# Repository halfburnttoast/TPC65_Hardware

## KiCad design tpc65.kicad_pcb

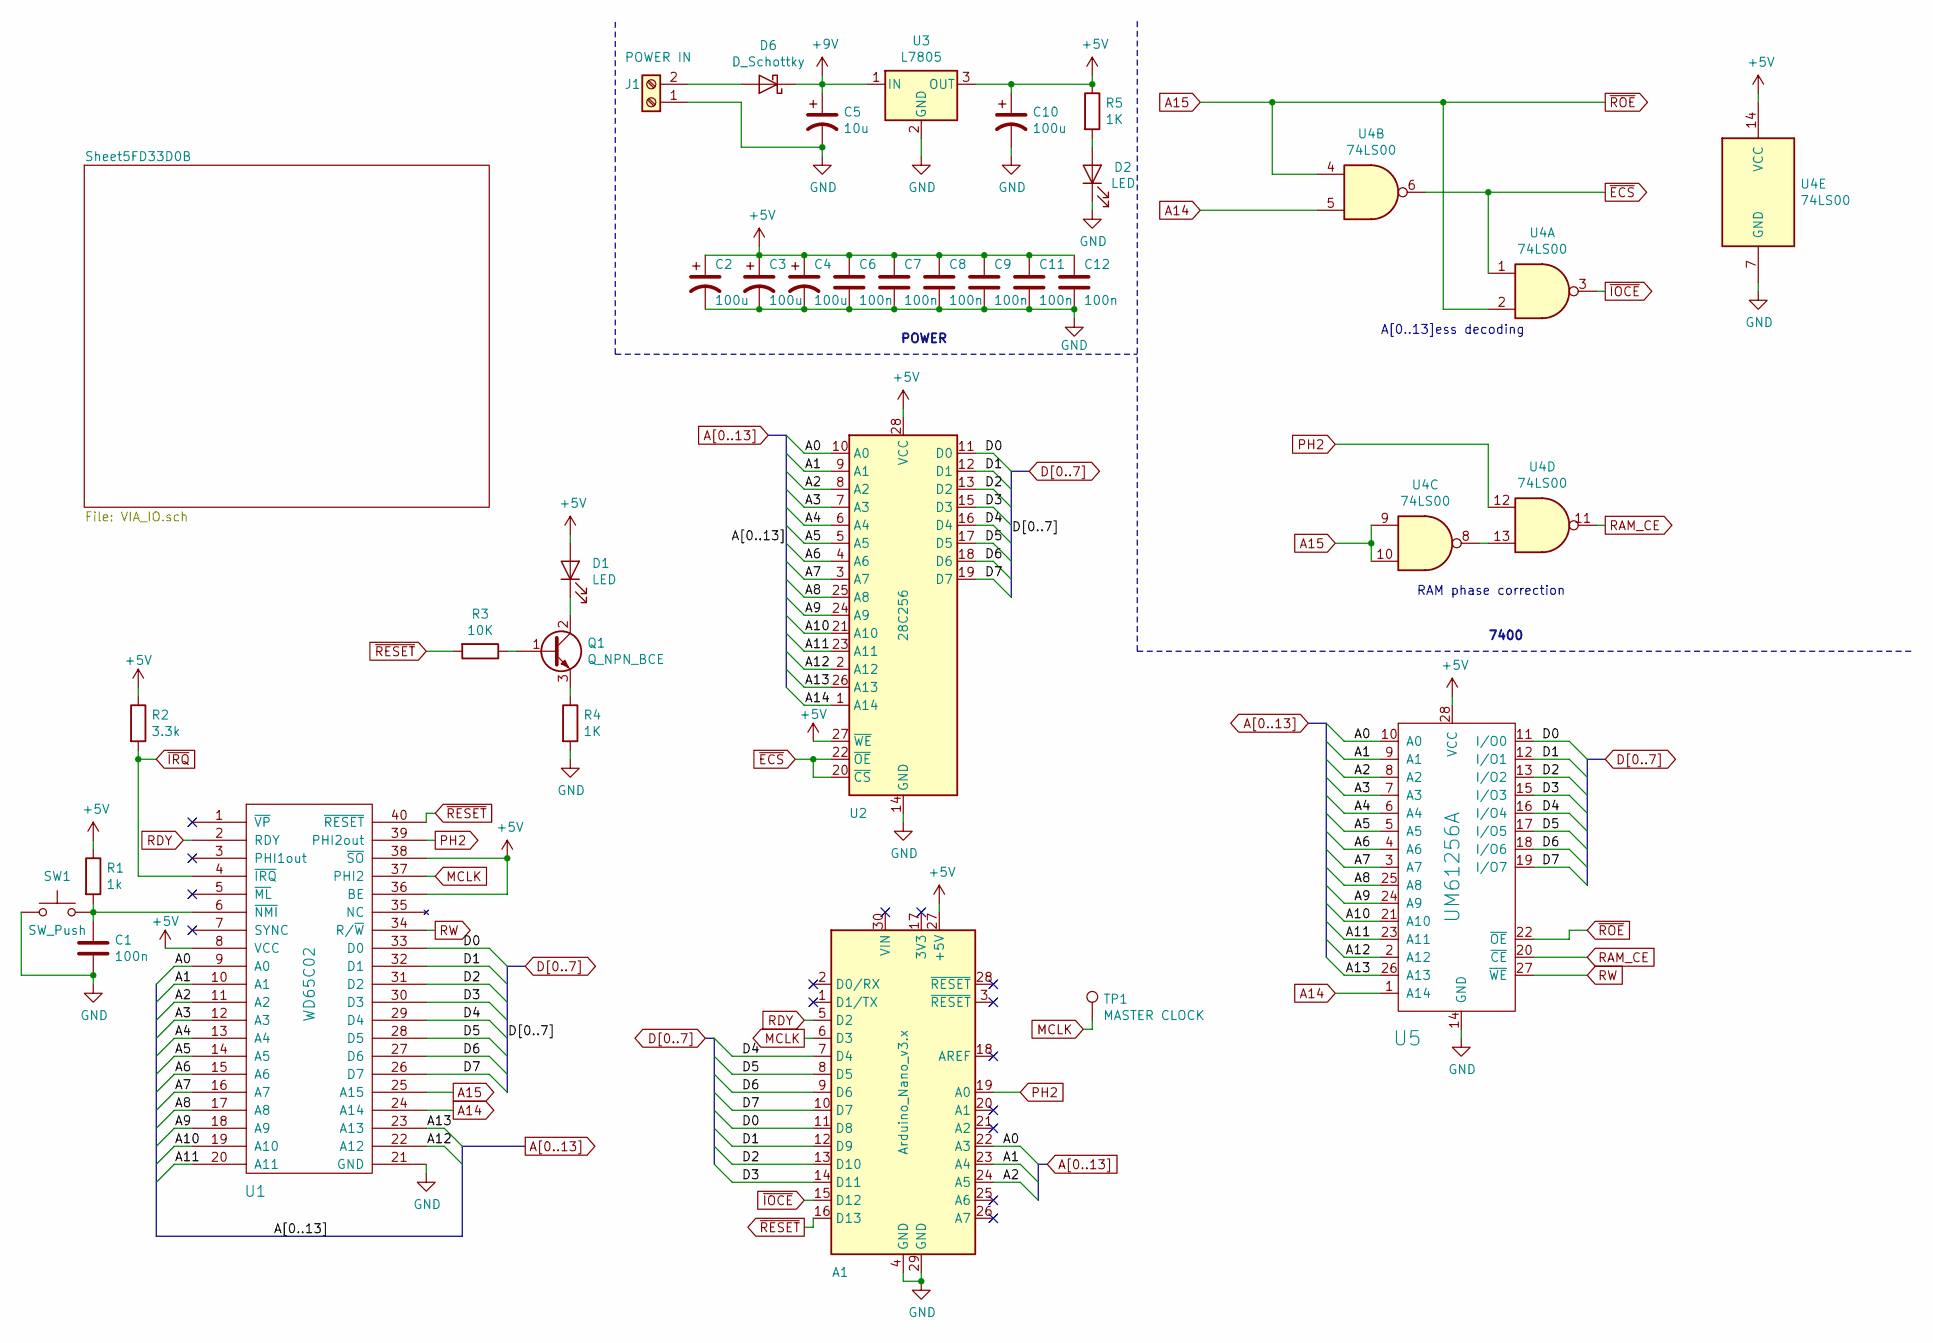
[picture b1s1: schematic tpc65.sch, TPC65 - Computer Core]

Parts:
A1: Arduino_Nano_v3.x; Arduino_Nano
C1, C6, C7, C8, C9, C11, C12: 100n; C_Disc_D4.3mm_W1.9mm_P5.00mm
C2, C3, C4, C10: 100u; CP_Radial_D5.0mm_P2.00mm
C5: 10u; CP_Radial_D5.0mm_P2.00mm
D1: LED; LED_1206_3216Metric_Pad1.42x1.75mm_HandSolder
D2: LED; LED_D5.0mm
D6: D_Schottky; D_SOD-123
J1: POWER IN; TerminalBlock_bornier-2_P5.08mm
Q1: Q_NPN_BCE; SOT-23_Handsoldering
R1: 1k; R_Axial_DIN0207_L6.3mm_D2.5mm_P7.62mm_Horizontal
R2: 3.3k; R_Axial_DIN0207_L6.3mm_D2.5mm_P7.62mm_Horizontal
R3: 10K; R_1206_3216Metric_Pad1.42x1.75mm_HandSolder
R4: 1K; R_1206_3216Metric_Pad1.42x1.75mm_HandSolder
R5: 1K; R_Axial_DIN0207_L6.3mm_D2.5mm_P7.62mm_Horizontal
SW1: SW_Push; SW_PUSH_6mm
TP1: MASTER CLOCK; TestPoint_Pad_1.0x1.0mm
U1: WD65C02; DIP-40_W15.24mm_Socket
U2: 28C256; DIP-28_W15.24mm_Socket
U3: L7805; TO-220F-3_Horizontal_TabDown
U4: 74LS00; DIP-14_W7.62mm_Socket
U5: UM61256A; DIP-28_W7.62mm_Socket

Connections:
+5V: A1.27 (+5V), C2.1, C3.1, C4.1, C6.1, C7.1, C8.1, C9.1, C10.1, C11.1, C12.1, D1.2 (A), R1.1, R2.1, R5.1, U1.8 (VCC), U1.36 (BE), U1.38 (~SO), U2.27 (~WE), U2.28 (VCC), U3.3 (OUT), U4.14 (VCC), U5.28 (VCC); also elsewhere on the board
+9V: C5.1, D6.1 (K), U3.1 (IN)
A0: A1.22 (A3), U1.9 (A0), U2.10 (A0), U5.10 (A0)
A1: A1.23 (A4), U1.10 (A1), U2.9 (A1), U5.9 (A1)
A2: A1.24 (A5), U1.11 (A2), U2.8 (A2), U5.8 (A2)
A3: U1.12 (A3), U2.7 (A3), U5.7 (A3); also elsewhere on the board
A4: U1.13 (A4), U2.6 (A4), U5.6 (A4); also elsewhere on the board
A5: U1.14 (A5), U2.5 (A5), U5.5 (A5); also elsewhere on the board
A6: U1.15 (A6), U2.4 (A6), U5.4 (A6); also elsewhere on the board
A7: U1.16 (A7), U2.3 (A7), U5.3 (A7); also elsewhere on the board
A8: U1.17 (A8), U2.25 (A8), U5.25 (A8); also elsewhere on the board
A9: U1.18 (A9), U2.24 (A9), U5.24 (A9)
A10: U1.19 (A10), U2.21 (A10), U5.21 (A10)
A11: U1.20 (A11), U2.23 (A11), U5.23 (A11)
A12: U1.22 (A12), U2.2 (A12), U5.2 (A12)
A13: U1.23 (A13), U2.26 (A13), U5.26 (A13)
A14: U1.24 (A14), U2.1 (A14), U4.5, U5.1 (A14)
A15: U1.25 (A15), U4.2, U4.4, U4.9, U4.10, U5.22 (~OE)
D0: A1.11 (D8), U1.33 (D0), U2.11 (D0), U5.11 (I/O0); also elsewhere on the board
D1: A1.12 (D9), U1.32 (D1), U2.12 (D1), U5.12 (I/O1); also elsewhere on the board
D2: A1.13 (D10), U1.31 (D2), U2.13 (D2), U5.13 (I/O2); also elsewhere on the board
D3: A1.14 (D11), U1.30 (D3), U2.15 (D3), U5.15 (I/O3); also elsewhere on the board
D4: A1.7 (D4), U1.29 (D4), U2.16 (D4), U5.16 (I/O4); also elsewhere on the board
D5: A1.8 (D5), U1.28 (D5), U2.17 (D5), U5.17 (I/O5); also elsewhere on the board
D6: A1.9 (D6), U1.27 (D6), U2.18 (D6), U5.18 (I/O6); also elsewhere on the board
D7: A1.10 (D7), U1.26 (D7), U2.19 (D7), U5.19 (I/O7); also elsewhere on the board
GND: A1.4 (GND), A1.29 (GND), C1.2, C2.2, C3.2, C4.2, C5.2, C6.2, C7.2, C8.2, C9.2, C10.2, C11.2, C12.2, D2.1 (K), J1.1, R4.2, SW1.1, U1.21 (GND), U2.14 (GND), U3.2 (GND), U4.7 (GND), U5.14 (GND); also elsewhere on the board
MCLK: A1.6 (D3), TP1.1, U1.37 (PHI2)
unnamed: C1.1, R1.2, SW1.2, U1.6 (~NMI)
unnamed: D1.1 (K), Q1.2 (C)
unnamed: D2.2 (A), R5.2
unnamed: D6.2 (A), J1.2
unnamed: Q1.1 (B), R3.1
unnamed: Q1.3 (E), R4.1
unnamed: U4.8, U4.13
PH2: A1.19 (A0), U1.39 (PHI2out), U4.12; also elsewhere on the board
RAM_CE: U4.11, U5.20 (~CE)
RDY: A1.5 (D2), U1.2 (RDY)
RW: U1.34 (R/~W), U5.27 (~WE); also elsewhere on the board
~ECS: U2.20 (~CS), U2.22 (~OE), U4.1, U4.6
~IOCE: A1.15 (D12), U4.3; also elsewhere on the board
~IRQ: R2.2, U1.4 (~IRQ); also elsewhere on the board
~RESET: A1.16 (D13), R3.2, U1.40 (~RESET); also elsewhere on the board

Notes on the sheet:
RAM phase correction
A[0..13]ess decoding
7400
POWER

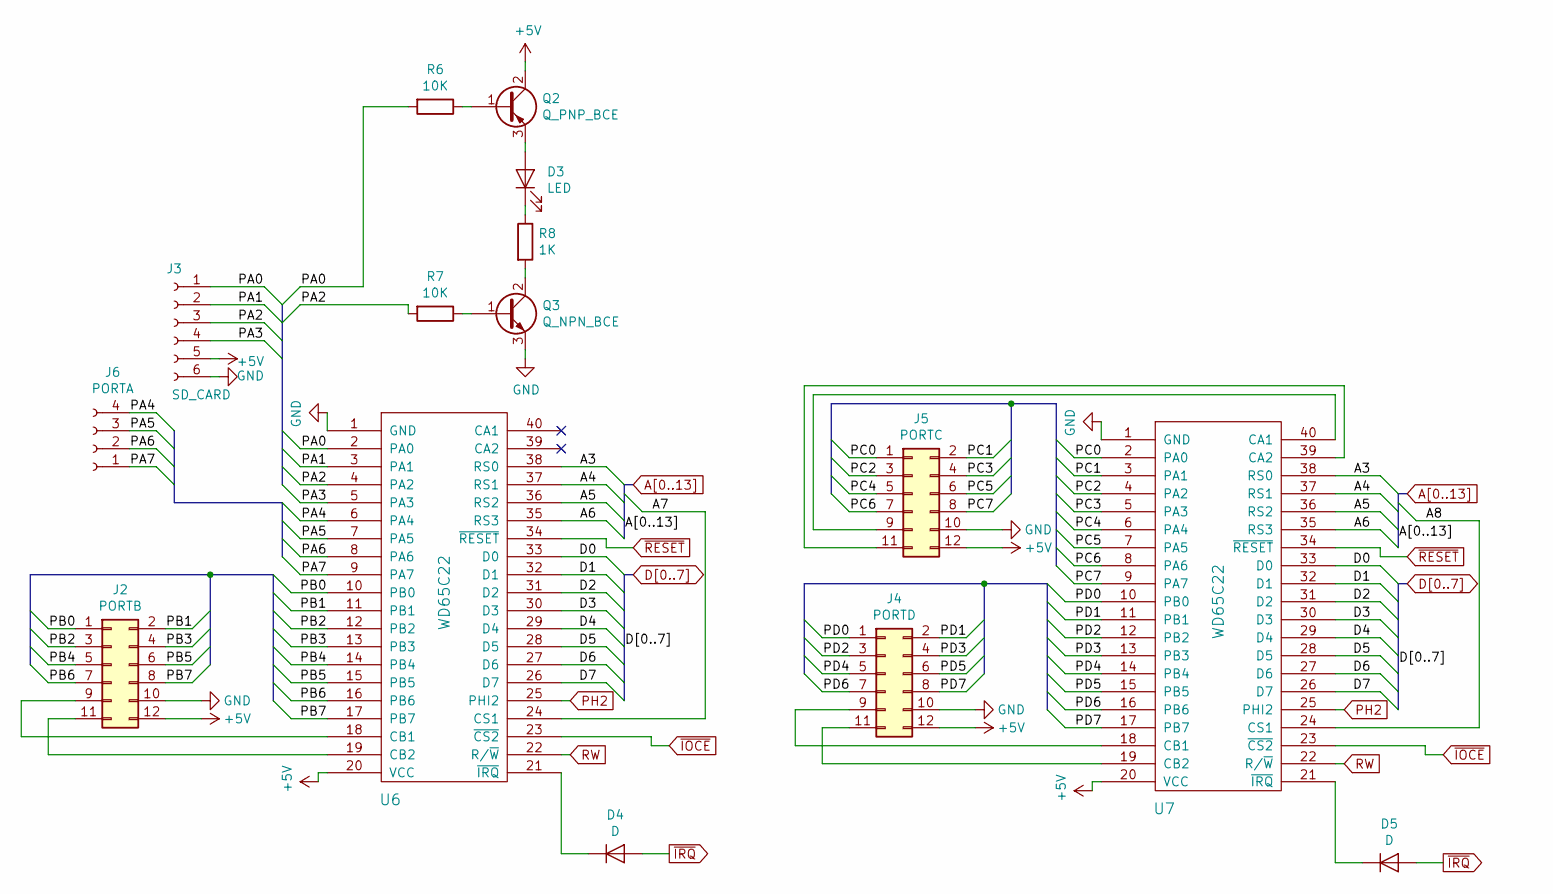
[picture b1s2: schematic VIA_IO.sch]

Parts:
D3: LED; LED_1206_3216Metric_Pad1.42x1.75mm_HandSolder
D4, D5: D; D_T-1_P5.08mm_Horizontal
J2: PORTB; PinSocket_2x06_P2.54mm_Vertical
J3: SD_CARD; PinSocket_1x06_P2.54mm_Vertical
J4: PORTD; PinSocket_2x06_P2.54mm_Vertical
J5: PORTC; PinSocket_2x06_P2.54mm_Vertical
J6: PORTA; PinSocket_2x02_P2.54mm_Vertical
Q2: Q_PNP_BCE; SOT-23_Handsoldering
Q3: Q_NPN_BCE; SOT-23_Handsoldering
R6, R7: 10K; R_1206_3216Metric_Pad1.42x1.75mm_HandSolder
R8: 1K; R_1206_3216Metric_Pad1.42x1.75mm_HandSolder
U6, U7: WD65C22; DIP-40_W15.24mm_Socket

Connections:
+5V: J2.12, J3.5, J4.12, J5.12, Q2.2 (C), U6.20 (VCC), U7.20 (VCC); also elsewhere on the board
/Sheet5FD33D0B/PA0: J3.1, R6.2, U6.2 (PA0)
/Sheet5FD33D0B/PA1: J3.2, U6.3 (PA1)
/Sheet5FD33D0B/PA2: J3.3, R7.2, U6.4 (PA2)
/Sheet5FD33D0B/PA3: J3.4, U6.5 (PA3)
/Sheet5FD33D0B/PA4: J6.4, U6.6 (PA4)
/Sheet5FD33D0B/PA5: J6.3, U6.7 (PA5)
/Sheet5FD33D0B/PA6: J6.2, U6.8 (PA6)
/Sheet5FD33D0B/PA7: J6.1, U6.9 (PA7)
/Sheet5FD33D0B/PB0: J2.1, U6.10 (PB0)
/Sheet5FD33D0B/PB1: J2.2, U6.11 (PB1)
/Sheet5FD33D0B/PB2: J2.3, U6.12 (PB2)
/Sheet5FD33D0B/PB3: J2.4, U6.13 (PB3)
/Sheet5FD33D0B/PB4: J2.5, U6.14 (PB4)
/Sheet5FD33D0B/PB5: J2.6, U6.15 (PB5)
/Sheet5FD33D0B/PB6: J2.7, U6.16 (PB6)
/Sheet5FD33D0B/PB7: J2.8, U6.17 (PB7)
/Sheet5FD33D0B/PC0: J5.1, U7.2 (PA0)
/Sheet5FD33D0B/PC1: J5.2, U7.3 (PA1)
/Sheet5FD33D0B/PC2: J5.3, U7.4 (PA2)
/Sheet5FD33D0B/PC3: J5.4, U7.5 (PA3)
/Sheet5FD33D0B/PC4: J5.5, U7.6 (PA4)
/Sheet5FD33D0B/PC5: J5.6, U7.7 (PA5)
/Sheet5FD33D0B/PC6: J5.7, U7.8 (PA6)
/Sheet5FD33D0B/PC7: J5.8, U7.9 (PA7)
/Sheet5FD33D0B/PD0: J4.1, U7.10 (PB0)
/Sheet5FD33D0B/PD1: J4.2, U7.11 (PB1)
/Sheet5FD33D0B/PD2: J4.3, U7.12 (PB2)
/Sheet5FD33D0B/PD3: J4.4, U7.13 (PB3)
/Sheet5FD33D0B/PD4: J4.5, U7.14 (PB4)
/Sheet5FD33D0B/PD5: J4.6, U7.15 (PB5)
/Sheet5FD33D0B/PD6: J4.7, U7.16 (PB6)
/Sheet5FD33D0B/PD7: J4.8, U7.17 (PB7)
A3: U6.38 (RS0), U7.38 (RS0); also elsewhere on the board
A4: U6.37 (RS1), U7.37 (RS1); also elsewhere on the board
A5: U6.36 (RS2), U7.36 (RS2); also elsewhere on the board
A6: U6.35 (RS3), U7.35 (RS3); also elsewhere on the board
A7: U6.24 (CS1); also elsewhere on the board
A8: U7.24 (CS1); also elsewhere on the board
D0: U6.33 (D0), U7.33 (D0); also elsewhere on the board
D1: U6.32 (D1), U7.32 (D1); also elsewhere on the board
D2: U6.31 (D2), U7.31 (D2); also elsewhere on the board
D3: U6.30 (D3), U7.30 (D3); also elsewhere on the board
D4: U6.29 (D4), U7.29 (D4); also elsewhere on the board
D5: U6.28 (D5), U7.28 (D5); also elsewhere on the board
D6: U6.27 (D6), U7.27 (D6); also elsewhere on the board
D7: U6.26 (D7), U7.26 (D7); also elsewhere on the board
GND: J2.10, J3.6, J4.10, J5.10, Q3.3 (E), U6.1 (GND), U7.1 (GND); also elsewhere on the board
unnamed: D3.1 (K), R8.1
unnamed: D3.2 (A), Q2.3 (E)
unnamed: D4.1 (K), U6.21 (~IRQ)
unnamed: D5.1 (K), U7.21 (~IRQ)
unnamed: J2.9, U6.18 (CB1)
unnamed: J2.11, U6.19 (CB2)
unnamed: J4.9, U7.18 (CB1)
unnamed: J4.11, U7.19 (CB2)
unnamed: J5.9, U7.40 (CA1)
unnamed: J5.11, U7.39 (CA2)
unnamed: Q2.1 (B), R6.1
unnamed: Q3.1 (B), R7.1
unnamed: Q3.2 (C), R8.2
PH2: U6.25 (PHI2), U7.25 (PHI2); also elsewhere on the board
RW: U6.22 (R/~W), U7.22 (R/~W); also elsewhere on the board
~IOCE: U6.23 (~CS2), U7.23 (~CS2); also elsewhere on the board
~IRQ: D4.2 (A), D5.2 (A); also elsewhere on the board
~RESET: U6.34 (~RESET), U7.34 (~RESET); also elsewhere on the board

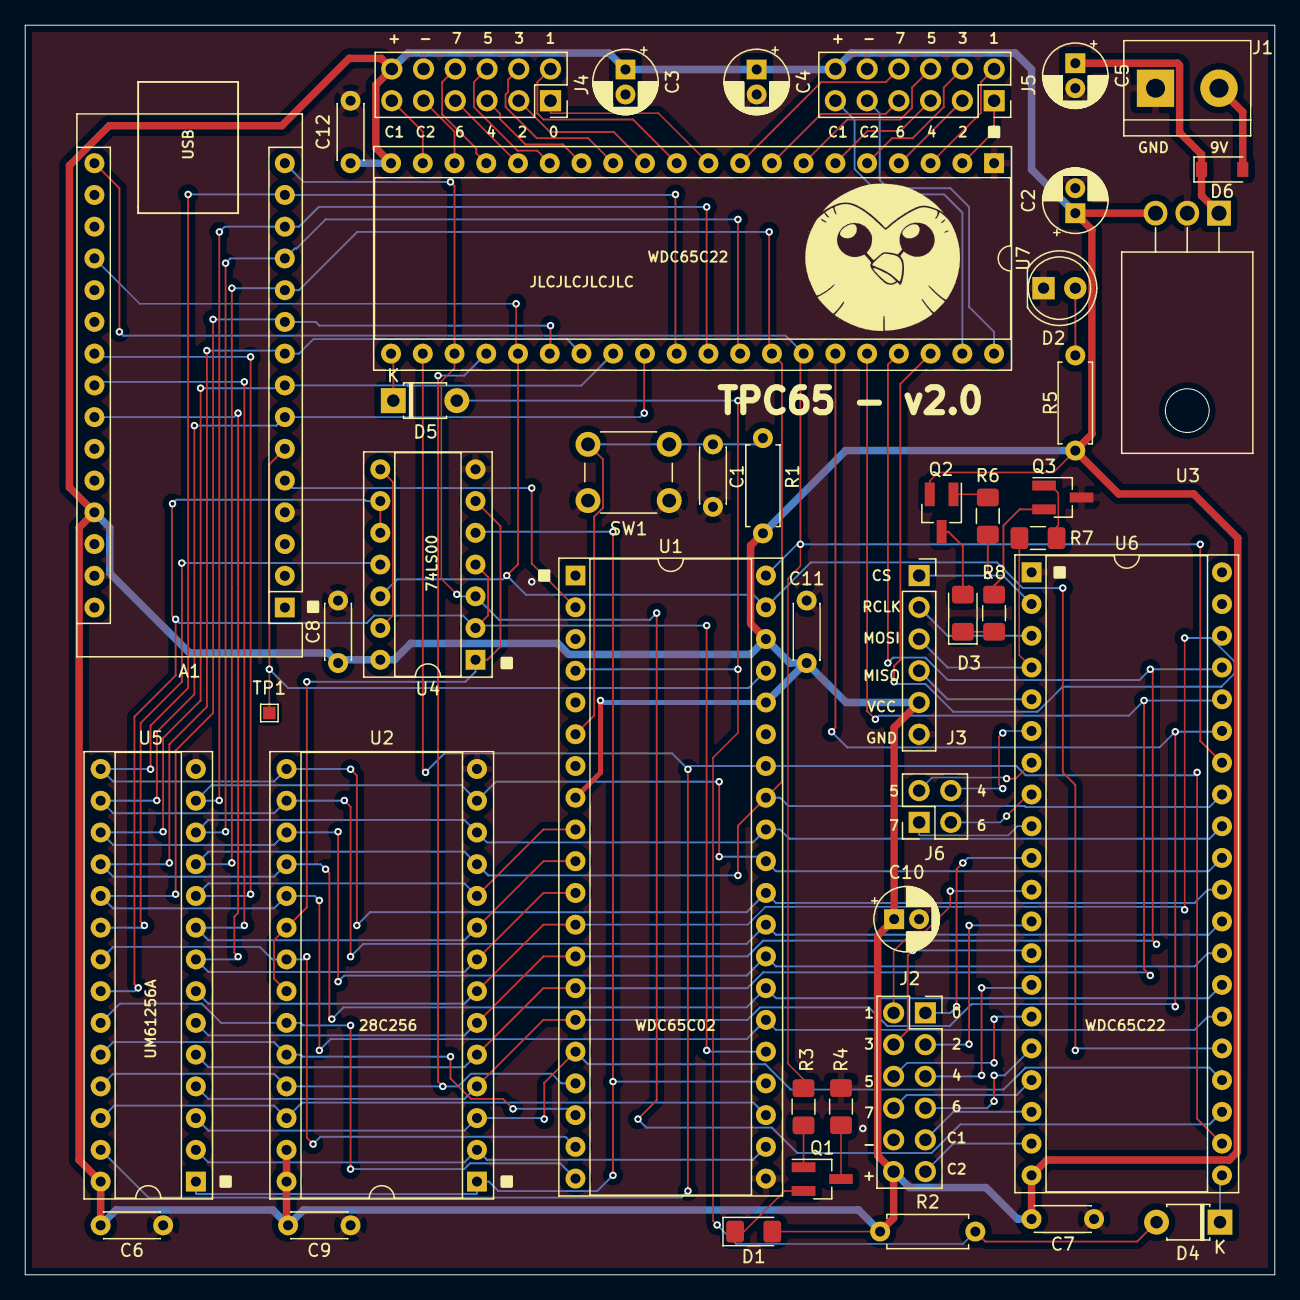
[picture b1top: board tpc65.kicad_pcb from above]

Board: 2 copper layers, 100.0 x 100.0 mm, 45 parts (0 on the bottom side), 88 nets.

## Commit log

2020-11-13 All project files added
